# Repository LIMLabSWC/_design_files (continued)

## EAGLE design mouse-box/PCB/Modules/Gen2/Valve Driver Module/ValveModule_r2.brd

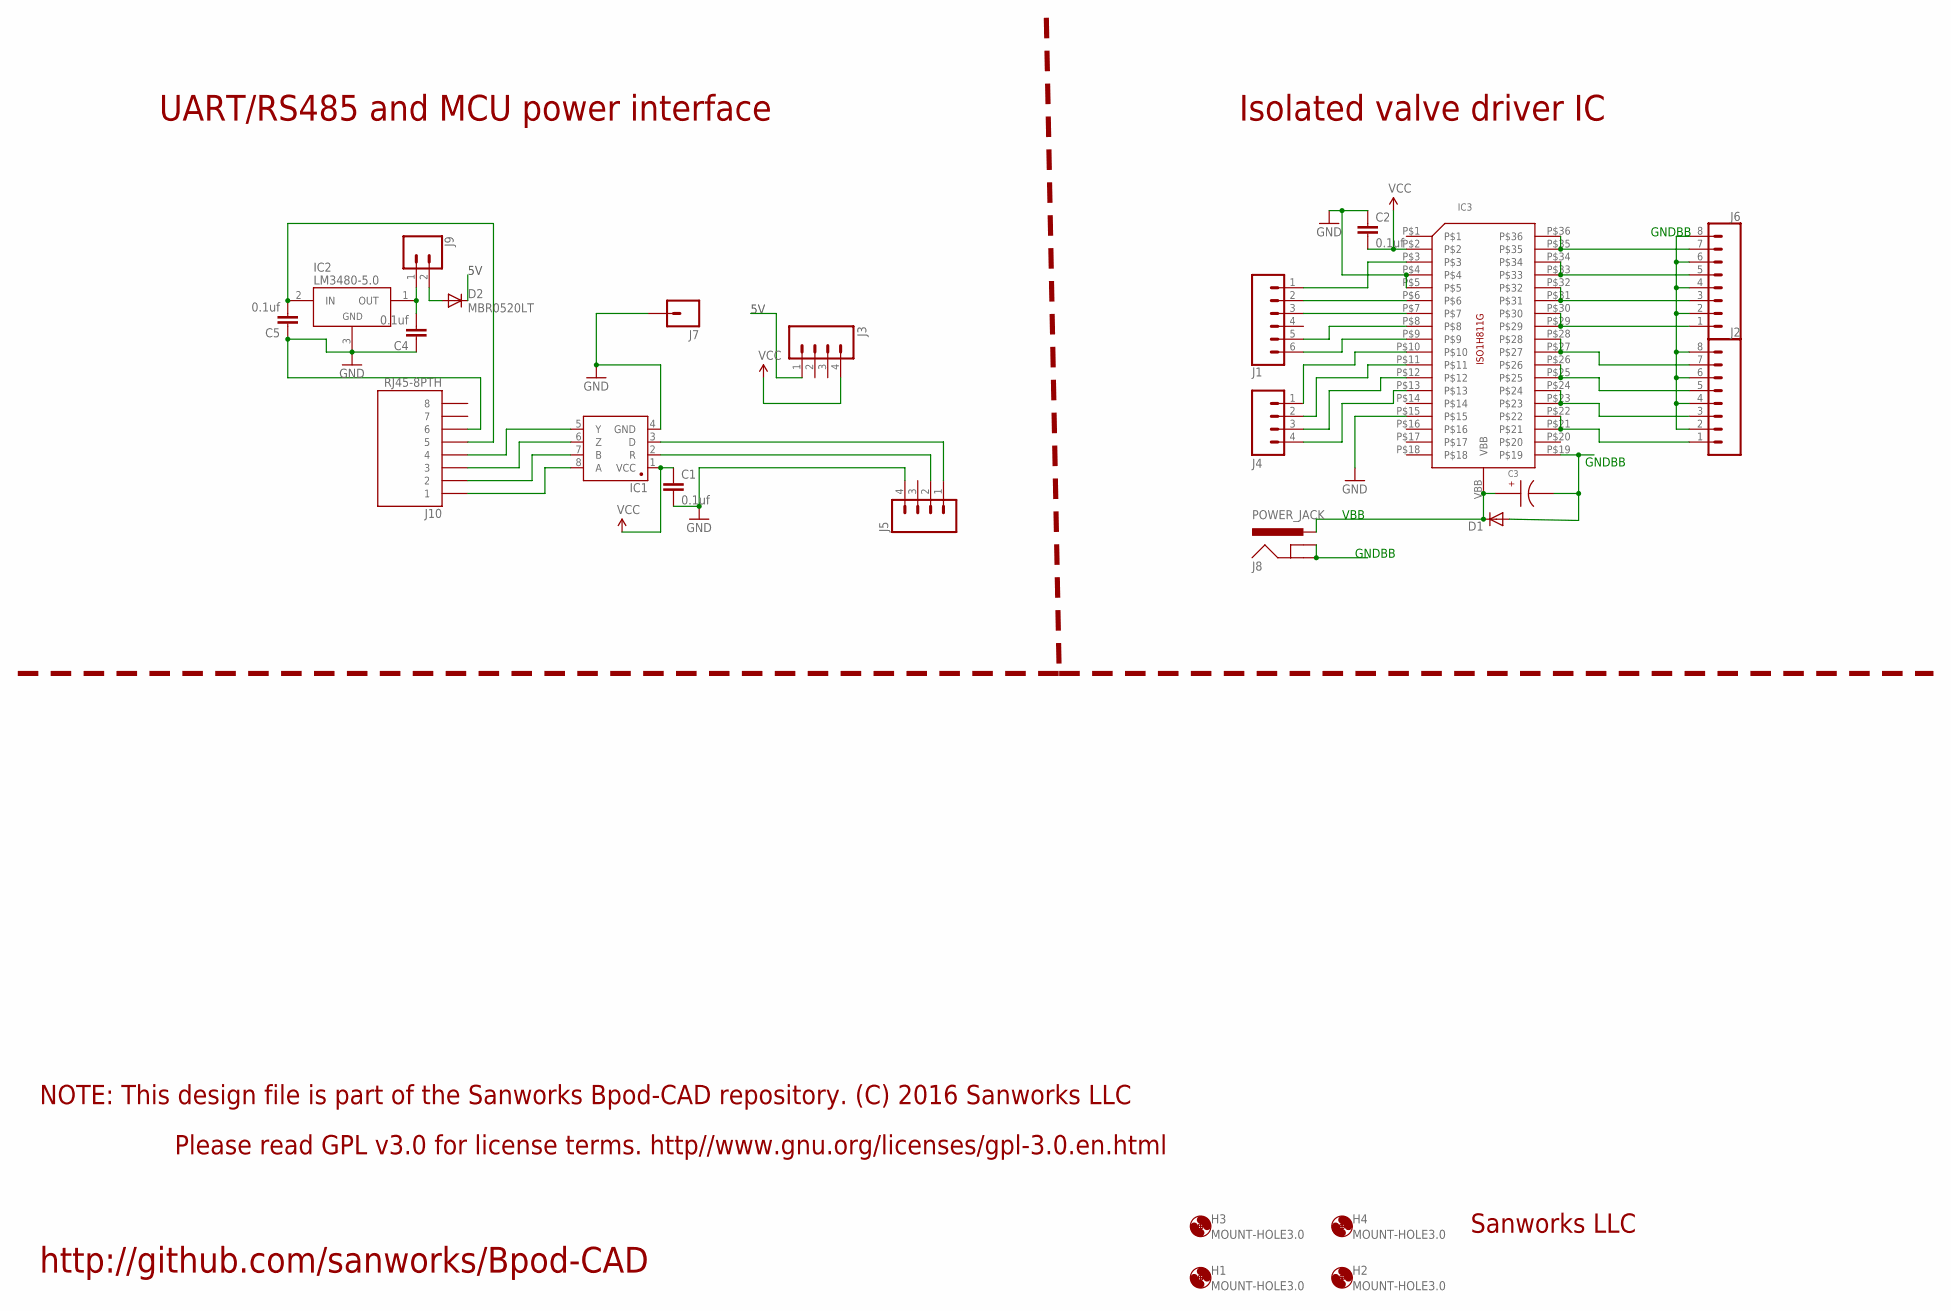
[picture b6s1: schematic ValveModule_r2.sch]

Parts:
C1, C2, C4, C5: 0.1uf; 1206
C3: EEE-FK1H100UR
D1: DIODE-DO214AA; DO214AA
D2: MBR0520LT; SOD123
H1, H2, H3, H4: MOUNT-HOLE3.0; 3,0
IC1: SN65HVD31DR; SO08
IC2: LM3480-5.0; SOT-23-3
IC3: ISO1H811G
J1: CONN_06SILK_FEMALE_PTH; 1X06
J2, J6: CONN_083.5MM-8; SCREWTERMINAL-3.5MM-8
J3, J4, J5: M04PTH; 1X04
J7: M01PTH; 1X01
J8: POWER_JACK; POWER_JACK_PTH
J9: CONN_02; 1X02
J10: RJ45-8PTH; RJ45-8

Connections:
5V: D2.C, J3.1
GND: C1.2, C2.1, C4.1, C5.1, IC1.4 (GND), IC2.3 (GND), IC3.P$4, IC3.P$5, IC3.P$15, J5.4, J7.1, J10.6
GNDBB: C3.CATHODE, D1.A, IC3.P$19, J2.2, J2.4, J2.6, J2.8, J6.2, J6.4, J6.6, J6.8, J8.GND, J8.GNDBREAK
unnamed: IC3.P$35, IC3.P$36, J6.7
unnamed: IC3.P$3, J1.1
unnamed: IC3.P$6, J1.2
unnamed: IC1.3 (D), J5.1
unnamed: IC3.P$7, J1.3
unnamed: IC1.2 (R), J5.2
unnamed: IC1.8 (A), J10.1
unnamed: IC1.7 (B), J10.2
unnamed: IC1.6 (Z), J10.3
unnamed: IC1.5 (Y), J10.4
unnamed: IC3.P$8, J1.5
unnamed: IC3.P$9, J1.6
unnamed: IC3.P$10, J4.1
unnamed: IC3.P$11, J4.2
unnamed: IC3.P$12, J4.3
unnamed: IC3.P$13, J4.4
unnamed: IC3.P$33, IC3.P$34, J6.5
unnamed: IC3.P$31, IC3.P$32, J6.3
unnamed: IC3.P$29, IC3.P$30, J6.1
unnamed: IC3.P$27, IC3.P$28, J2.7
unnamed: IC3.P$25, IC3.P$26, J2.5
unnamed: IC3.P$23, IC3.P$24, J2.3
unnamed: IC3.P$21, IC3.P$22, J2.1
unnamed: C5.2, IC2.2 (IN), J10.5
unnamed: C4.2, IC2.1 (OUT), J9.1
unnamed: D2.A, J9.2
VBB: C3.ANODE, D1.C, IC3.VBB, J8.PWR
VCC: C1.1, C2.2, IC1.1 (VCC), IC3.P$2, J3.4

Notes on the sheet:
VBB
GNDBB
UART/RS485 and MCU power interface
Isolated valve driver IC
Please read GPL v3.0 for license terms. http//www.gnu.org/licenses/gpl-3.0.en.html
NOTE: This design file is part of the Sanworks Bpod-CAD repository. (C) 2016 Sanworks LLC
Sanworks LLC
http://github.com/sanworks/Bpod-CAD

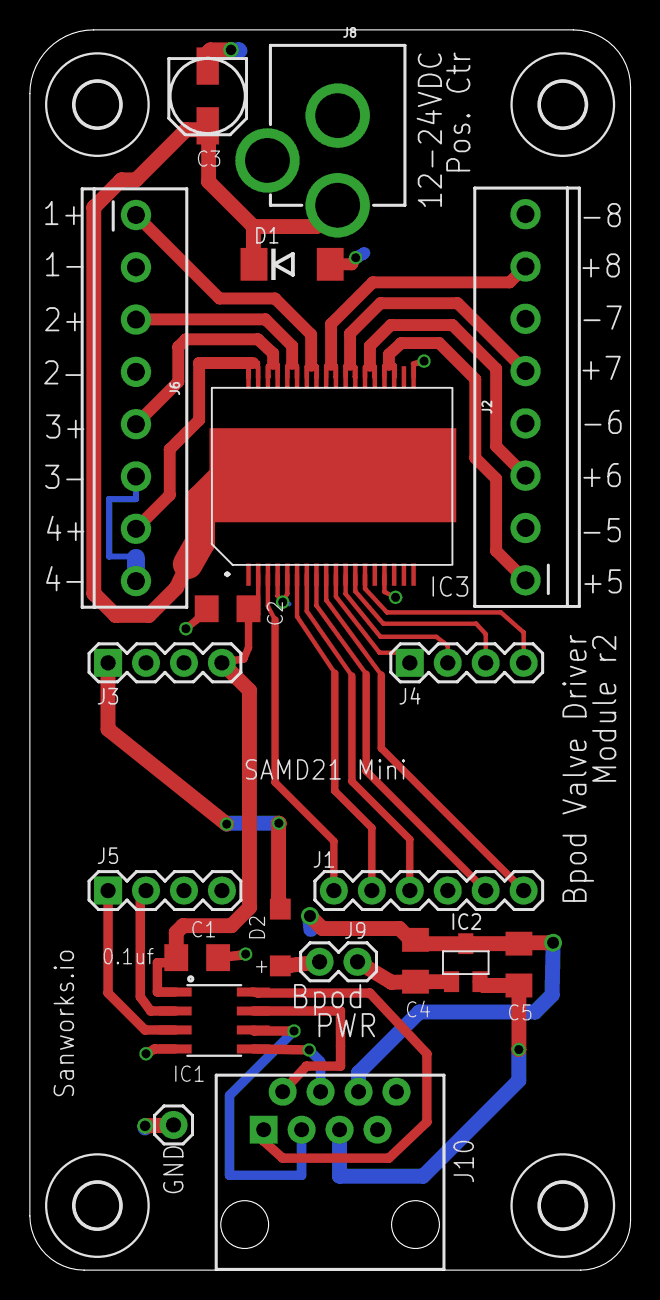
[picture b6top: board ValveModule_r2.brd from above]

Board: 2 copper layers, 40.2 x 83.0 mm, 24 parts (0 on the bottom side), 31 nets.
